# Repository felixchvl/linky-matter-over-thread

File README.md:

# linky-matter-over-thread

A small board that connects to the TIC output of a French Linky meter and makes its readings available over Thread, as a Matter device. It is powered by the meter itself, so there is no battery to replace and no power supply to run to the meter.

## Why I made it

I wanted my electricity usage in Home Assistant, live and without any cloud. The usual options are a Zigbee dongle (ZLinky), a Wi-Fi board that needs a USB supply next to the meter, or the Enedis website a day later. My home already runs a Thread network, and Home Assistant reads Matter energy measurements natively (kWh for the Energy dashboard, plus W, VA and V). So this board speaks Thread and Matter, and nothing else.

The closest thing I found is [BDeliers' Elektor Labs entry](https://www.elektormagazine.com/labs/the-electric-meter-that-matters) from 2024, which runs Matter over Thread on an STM32WB dev kit. The kit draws more than the TIC can supply, so it needs its own power. Running from the meter alone is the whole point of this one.

## Status

- [x] Schematic, v1
- [x] PCB layout, v1 (DRC clean, matches the schematic)
- [ ] First boards ordered and soldered
- [ ] Firmware (Zephyr / nRF Connect SDK, Matter over Thread)
  - [x] TIC decoder for both modes, with host tests
  - [x] Board definition and Matter application, building with nRF Connect SDK v3.4.2
  - [x] Energy per tariff index in Matter (HC/HP, Tempo, up to 10 indexes)
  - [ ] Running on a real board
- [x] Case designed in FreeCAD, checked against the board's 3D model (not printed yet)

Nothing has been built yet, so treat it as a design in progress. Read the checklist under [Building one](#building-one) before ordering.

## How it works

The TIC output has three screw terminals. I1 and A provide a little power (at least 130 mW, 6 V rms at 50 kHz). I1 and I2 carry the data as a 50 kHz carrier: carrier present means bit 0. The format is 7E1, at 1200 baud in "historique" mode or 9600 baud in "standard" mode.

**Power.** Two BAT54S form a Schottky bridge on I1–A. A 20 V zener keeps the input well under the 28 V limit of the regulator. A 470 µF capacitor covers the radio's transmit peaks, and a Microchip MCP1804 LDO (SOT-223) makes 3.3 V. With a linear regulator, current is what matters: the TIC can deliver roughly 16–20 mA, and the board should average 1–2 mA as a sleepy Thread device. JP1 links the regulator to the 3.3 V rail. Pull it to run the board from the programming header, or to put an ammeter in its place.

**Data.** The receiver is the stage from Charles-Henri Hallard's PiTInfo: a 2 kΩ trimmer, an LTV-814 optocoupler and a small N-MOSFET (an AO3400A here, a CJ2302 on the PiTInfo). When the carrier is present, TIC_RX goes low, so the UART reads the bits without any inversion. R1, on the MOSFET gate, is 3.3 kΩ as on the PiTInfo since V1.3a: with the 10 kΩ of V1.2 the optocoupler switches off too slowly for 9600 baud. The nRF52840 UART has no 7-bit mode, so the firmware reads 8 bits, checks the parity bit itself and drops it. On top of that, the checksum at the end of each TIC line catches errors. The firmware also keeps the 32 MHz crystal running while it reads the TIC, because the internal RC clock is too loose for 9600 baud.

**Radio.** The radio is an Ebyte E73-2G4M08S1C module with an nRF52840:
- normal voltage mode (VDDH tied to VDD), USB unused;
- a 32.768 kHz crystal (9 pF load, 3.2 × 1.5 mm) with 10 pF capacitors, for accurate wake-ups while sleeping. Nordic's reference uses 12 pF, which Reichelt does not stock in 0805; the lighter load runs the crystal 10 to 35 ppm fast, and cold slows it down, so the firmware declares a 100 ppm clock instead of 50;
- only the 28 castellated pads on the module's edge are used, so it solders with a regular iron; the 15 pads underneath stay unconnected.

The firmware will also read its own input voltage through a divider on AIN6. It will run as a sleepy end device by default, and only become a Thread router if the measured margin allows it.

## Pin assignment

| Signal | nRF52840 | E73 pad |
| --- | --- | --- |
| TIC_RX (UART RX) | P0.13 | 33 |
| Debug UART TX | P0.24 | 35 |
| VIN_SENSE (VIN × 0.13) | P0.30 / AIN6 | 10 |
| Button (to GND, internal pull-up) | P0.02 | 7 |
| LED (active high) | P1.10 | 2 |
| 32.768 kHz crystal | P0.00, P0.01 | 11, 13 |
| Reset | P0.18 | 26 |
| SWDIO, SWDCLK | | 37, 39 |

J2 is a 2.54 mm header, in the same order as the module pads: 3V3, GND, RST, TX, DIO, CLK.

## Files

```
hardware/
  linky-matter-over-thread.kicad_pro, .kicad_sch, .kicad_pcb  KiCad 10 project
  linky-matter-over-thread.kicad_sym, .pretty/                E73 symbol and footprint
  linky-matter-over-thread.3dshapes/                          simplified 3D model of the module
  production/linky-matter-over-thread-gerbers.zip             Gerbers and drill files
  production/bom.csv                                          parts list with Reichelt article numbers
firmware/                                                   Zephyr / nRF Connect SDK app, see firmware/README.md
case/                                                       3D-printed enclosure (FreeCAD), see case/README.md
docs/
  schematic.pdf
  images/
```

| Top | Bottom |
| --- | --- |
|  |  |

The copper alone, with the ground pour hidden so the tracks are easy to follow. The bottom layer is seen through the board, in the same orientation as the top.

| Top copper | Bottom copper |
| --- | --- |
|  |  |

The full schematic is in [docs/schematic.pdf](docs/schematic.pdf).

## Building one

The board is 64 × 41 mm, two layers, 1.6 mm. The Gerber zip can be uploaded as is to JLCPCB or any other fab. JLCPCB no longer adds an order number by default ("Mark on PCB: Remove Mark"), so the board has no placeholder for one.

Tracks are 0.5 mm for power and ground, 0.4 mm for signals and 0.3 mm on the module's pads, with at least 0.25 mm between copper, well clear of standard process limits. Silkscreen text is at least 1 mm high with a 0.15 mm stroke. The rules are saved in the KiCad project (Default and Power netclasses), so edits in KiCad pick them up. There is no copper on either layer between the module's antenna end and the board edge.

To regenerate the Gerber zip after a change, from `hardware/`:

```
kicad-cli pcb export gerbers --layers F.Cu,B.Cu,F.Paste,B.Paste,F.SilkS,B.SilkS,F.Mask,B.Mask,Edge.Cuts --subtract-soldermask -o gerbers/ linky-matter-over-thread.kicad_pcb
kicad-cli pcb export drill --format excellon --excellon-units mm --excellon-separate-th --generate-map --map-format gerberx2 -o gerbers/ linky-matter-over-thread.kicad_pcb
```

Then zip the contents of `gerbers/` into `production/linky-matter-over-thread-gerbers.zip`.

Before ordering:

- The E73 footprint is drawn from Ebyte's drawing. Its pads match the [SnapEDA footprint](https://github.com/rbaron/b-parasite/tree/main/kicad/lib/snapeda) and [nordic-lib-kicad](https://github.com/hlord2000/nordic-lib-kicad) exactly, and [nrfmicro](https://github.com/joric/nrfmicro)'s within 0.2 mm, but it has not met a physical module yet. If you have one, print [docs/footprint-check-1to1.pdf](docs/footprint-check-1to1.pdf) at 100 % (its two scale bars tell you if the printer resized it) and lay the module on it.
- The E73 is no longer listed at LCSC, and Passion Radio has run out. [Micros](https://www.micros.com.pl/en/product/rf-e73-2g4m08s1c,355348.html) (Poland) and [Ebyte's own store](https://ebyteiot.com/products/2-4ghz-ble-mesh-small-smd-e73-2g4m08s1c-nordic-nrf52840-module-small-size-ble-5-0) sell it. Make sure it is the E73-2G4M08S1C: the S1E carries an nRF52833, and the S1CX is a different variant.
- Every other part is stocked by Reichelt, an EU distributor. I picked it on purpose: since 2026, small parcels from China into France pay a flat customs fee per type of item, which costs more than the parts on an order like this one.

Parts:

- **[production/bom.csv](hardware/production/bom.csv)** has every part with a manufacturer part number and its Reichelt article number.
- **Passives:** generic 0805, any equivalent works. Add a 4.7 kΩ in case R1 needs tuning on your meter (see below).
- **Regulator:** the MCP1804 takes up to 28 V in (30 V absolute), which leaves a wide margin over the 20 V zener.

Soldering:

- All SMD parts are 0805, SOT-23, SOT-223, MiniMELF or a 3.2 × 1.5 mm crystal, with hand-soldering pads where KiCad has them.
- The 3.2 × 1.5 mm crystal and the 0805 parts are the smallest; a fine tip is enough, hot air helps.

Before connecting it to the meter:

- Set RV1 to about 1–1.2 kΩ. The TIC wants 500–2000 Ω on its data pair, and 1–1.2 kΩ is what people report working on Linky.
- Wire A, I1 and I2 as printed next to the terminal. I1 is in the middle because it feeds both the power bridge and the receiver, so the order differs from the meter's.
- Only use the meter's I1, I2 and A terminals. The dry contact (C1, C2) next to them can carry 230 V, and the board has no protection against it. With a standard off-peak contactor, its coil limits the current to about 13 mA. The board survives that, but it keeps the contactor on, so the water heater keeps heating. With any other wiring, RV1 can burn. A fuse would not help: in the standard case the fault current is about the same as the board's normal current.
- So before screwing the wires into the board, measure the AC voltage between each pair of wires (A–I1, I1–I2, A–I2) with a multimeter, during peak hours, while the dry contact is open (during off-peak hours C1–C2 reads 0 V). Nothing should read more than about 15 V. The TIC itself shows a few volts at most, often less because multimeters under-read its 50 kHz carrier. A reading near 230 V means a wire is on the wrong terminal.
- Never feed 3.3 V into J2 while JP1 is fitted.
- When a computer is plugged into J2 at the meter, run it on battery or through a USB isolator. The board's ground is tied to I1 and A through the bridge, so an earthed computer would tie the TIC to earth.

First power-up on the meter, if you have a multimeter and a scope:

- 3.3 V on the 3V3 test point, and VIN well above 4 V (the regulator needs 3.7 V).
- The 3.3 V rail should rise from 0 to 1.7 V in less than 60 ms, or the nRF52840's power-on reset may misbehave. If it is slower, a smaller C1 (220 µF) still covers the radio's peaks.
- TIC_RX on the RX test point, at 1200 baud (historique) and 9600 baud (standard): square edges, low while the carrier is on. If frames are missing, lower RV1 a little, but not under about 600 Ω so the TIC still sees more than 500 Ω. If the meter stays in historique mode and its signal is weak, R1 can go back up to 4.7 kΩ for more sensitivity.
- The average current, with an ammeter in place of JP1.

The module is programmed over SWD through J2, with a J-Link or a Raspberry Pi Pico running [debugprobe](https://github.com/raspberrypi/debugprobe).

## Credits

- The TIC receiver comes from [PiTInfo](https://github.com/hallard/teleinfo) by Charles-Henri Hallard.
- The electrical and frame details come from the Enedis TIC specification, Enedis-NOI-CPT_54E.
- The module pinout and pad drawing come from the Ebyte E73-2G4M08S1C user manual.
- Decoding in the firmware will start from [zephyr-linky-tic](https://github.com/lucasdietrich/zephyr-linky-tic) by Lucas Dietrich.

## License

The hardware design (everything outside `firmware/`) is shared under [CC BY-NC-SA 4.0](LICENSE), the same license as the PiTInfo design it builds on.

The firmware is under the [Apache License 2.0](firmware/LICENSE), like Zephyr.

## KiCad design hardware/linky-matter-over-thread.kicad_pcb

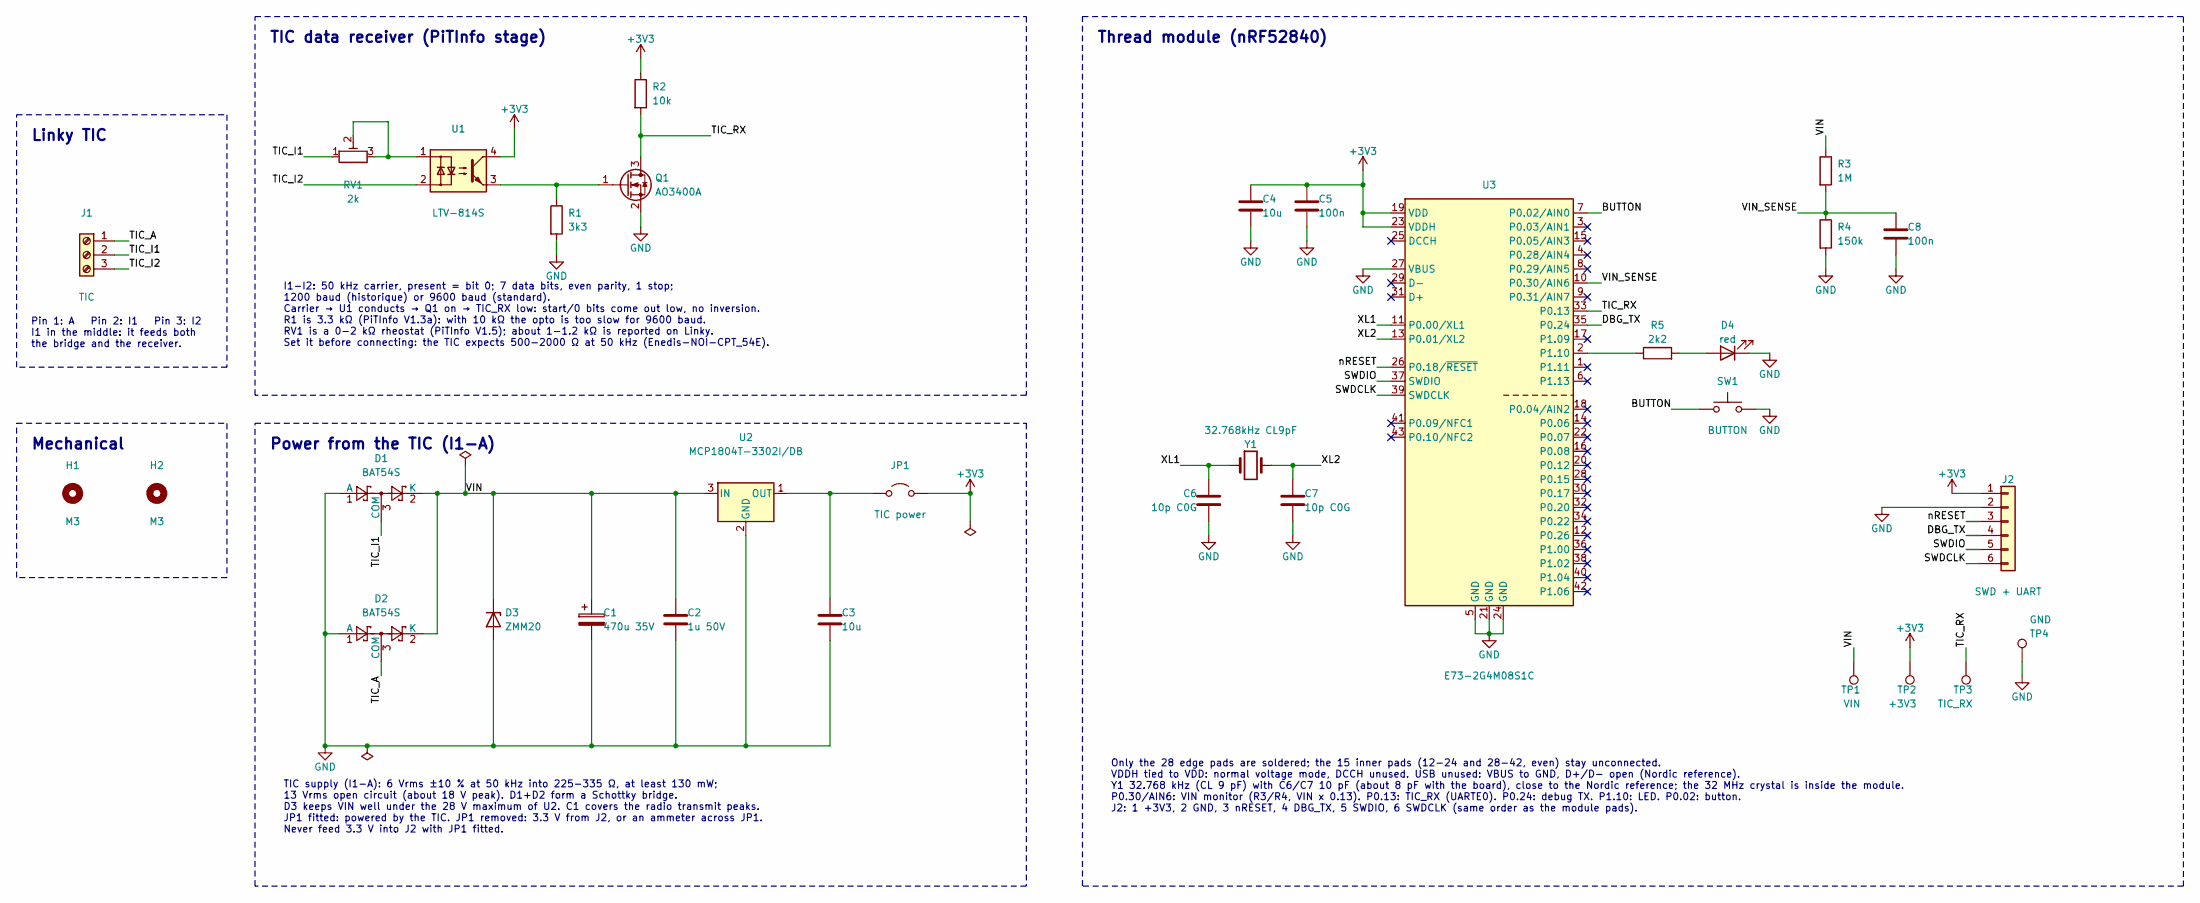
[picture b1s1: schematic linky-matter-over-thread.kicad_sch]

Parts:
C1: 470u 35V; CP_Radial_D10.0mm_P5.00mm; MPN RD1V477M10016BB100
C2: 1u 50V; C_0805_2012Metric_Pad1.18x1.45mm_HandSolder; MPN CL21B105KBFNNNE
C3, C4: 10u; C_0805_2012Metric_Pad1.18x1.45mm_HandSolder; MPN CL21B106KOQNNNE
C5, C8: 100n; C_0805_2012Metric_Pad1.18x1.45mm_HandSolder; MPN CL21B104KBCNNNC
C6, C7: 10p C0G; C_0805_2012Metric_Pad1.18x1.45mm_HandSolder; MPN CC0805JRNPO9BN100
D1, D2: BAT54S; SOT-23; MPN BAT54S-7-F
D3: ZMM20; D_MiniMELF; MPN ZMM20V (MiniMELF, 0.5 W)
D4: red; LED_0805_2012Metric_Pad1.15x1.40mm_HandSolder; MPN 17-21/R6C-AP1Q2L/3T
H1, H2: M3; MountingHole_3.2mm_M3
J1: TIC; TerminalBlock_Phoenix_MKDS-1,5-3-5.08_1x03_P5.08mm_Horizont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; MPN MKDS 1,5/ 3-5,08
J2: SWD + UART; PinHeader_1x06_P2.54mm_Vertical; MPN 6 pins cut from a 1x40 2.54 mm header
JP1: TIC power; PinHeader_1x02_P2.54mm_Vertical; MPN 2 pins cut from the same header, plus a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
Q1: AO3400A; SOT-23; MPN AO3400A
R1: 3k3; R_0805_2012Metric_Pad1.20x1.40mm_HandSolder; MPN 3.3 k 0805
R2: 10k; R_0805_2012Metric_Pad1.20x1.40mm_HandSolder; MPN 10 k 0805
R3: 1M; R_0805_2012Metric_Pad1.20x1.40mm_HandSolder; MPN 1 M 0805
R4: 150k; R_0805_2012Metric_Pad1.20x1.40mm_HandSolder; MPN 150 k 0805
R5: 2k2; R_0805_2012Metric_Pad1.20x1.40mm_HandSolder; MPN 2.2 k 0805
RV1: 2k; Potentiometer_Bourns_3296W_Vertical; MPN 64W 2 k multi-turn trimmer (3296W footp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
SW1: BUTTON; SW_PUSH_6mm; MPN DTS-62N (6 x 6 x 5 mm)
TP1: VIN; TestPoint_Pad_D1.5mm
TP2: +3V3; TestPoint_Pad_D1.5mm
TP3: TIC_RX; TestPoint_Pad_D1.5mm
TP4: GND; TestPoint_Pad_D1.5mm
U1: LTV-814S; SMDIP-4_W9.53mm; MPN LTV-814S
U2: MCP1804T-3302I/DB; SOT-223-3_TabPin2; MPN MCP1804T-3302I/DB
U3: E73-2G4M08S1C; MPN E73-2G4M08S1C
Y1: 32.768kHz CL9pF; Crystal_SMD_3215-2Pin_3.2x1.5mm; MPN CC7V-T1A 32.768 kHz 9 pF

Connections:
+3V3: C4.1, C5.1, J2.1, JP1.2 (B), R2.1, TP2.1, U1.4, U3.19 (VDD), U3.23 (VDDH)
/BUTTON: SW1.1, U3.7 (P0.02/AIN0)
/DBG_TX: J2.4, U3.35 (P0.24)
/SWDCLK: J2.6, U3.39 (SWDCLK)
/SWDIO: J2.5, U3.37 (SWDIO)
/TIC_A: D2.3 (COM), J1.1
/TIC_I1: D1.3 (COM), J1.2, RV1.1
/TIC_I2: J1.3, U1.2
/TIC_RX: Q1.3 (D), R2.2, TP3.1, U3.33 (P0.13)
/VIN: C1.1, C2.1, D1.2 (K), D2.2 (K), D3.1 (K), R3.1, TP1.1, U2.3 (IN)
/VIN_SENSE: C8.1, R3.2, R4.1, U3.10 (P0.30/AIN6)
/XL1: C6.1, U3.11 (P0.00/XL1), Y1.1
/XL2: C7.1, U3.13 (P0.01/XL2), Y1.2
/nRESET: J2.3, U3.26 (P0.18/~RESET)
GND: C1.2, C2.2, C3.2, C4.2, C5.2, C6.2, C7.2, C8.2, D1.1 (A), D2.1 (A), D3.2 (A), D4.1 (K), J2.2, Q1.2 (S), R1.2, R4.2, SW1.2, TP4.1, U2.2 (GND), U3.5 (GND), U3.21 (GND), U3.24 (GND), U3.27 (VBUS)
unnamed: D4.2 (A), R5.2
unnamed: C3.1, JP1.1 (A), U2.1 (OUT)
unnamed: Q1.1 (G), R1.1, U1.3
unnamed: RV1.2, RV1.3, U1.1
unnamed: R5.1, U3.2 (P1.10)

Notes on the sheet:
Power from the TIC (I1-A)
TIC data receiver (PiTInfo stage)
I1-I2: 50 kHz carrier, present = bit 0; 7 data bits, even parity, 1 stop; 1200 baud (historique) or 9600 baud (standard). Carrier → U1 conducts → Q1 on → TIC_RX low: start/0 bits come out low, no inversion. R1 is 3.3 kΩ (PiTInfo V1.3a): with 10 kΩ the opto is too slow for 9600 baud. RV1 is a 0-2 kΩ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
Thread module (nRF52840)
Only the 28 edge pads are soldered; the 15 inner pads (12-24 and 28-42, even) stay unconnected. VDDH tied to VDD: normal voltage mode, DCCH unused. USB unused: VBUS to GND, D+/D- open (Nordic reference). Y1 32.768 kHz (CL 9 pF) with C6/C7 10 pF (about 8 pF with the board), close to the Nordic refer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
TIC supply (I1-A): 6 Vrms ±10 % at 50 kHz into 225-335 Ω, at least 130 mW; 13 Vrms open circuit (about 18 V peak). D1+D2 form a Schottky bridge. D3 keeps VIN well under the 28 V maximum of U2. C1 covers the radio transmit peaks. JP1 fitted: powered by the TIC. JP1 removed: 3.3 V from J2, or an amme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
Linky TIC
Pin 1: A Pin 2: I1 Pin 3: I2 I1 in the middle: it feeds both the bridge and the receiver.
Mechanical

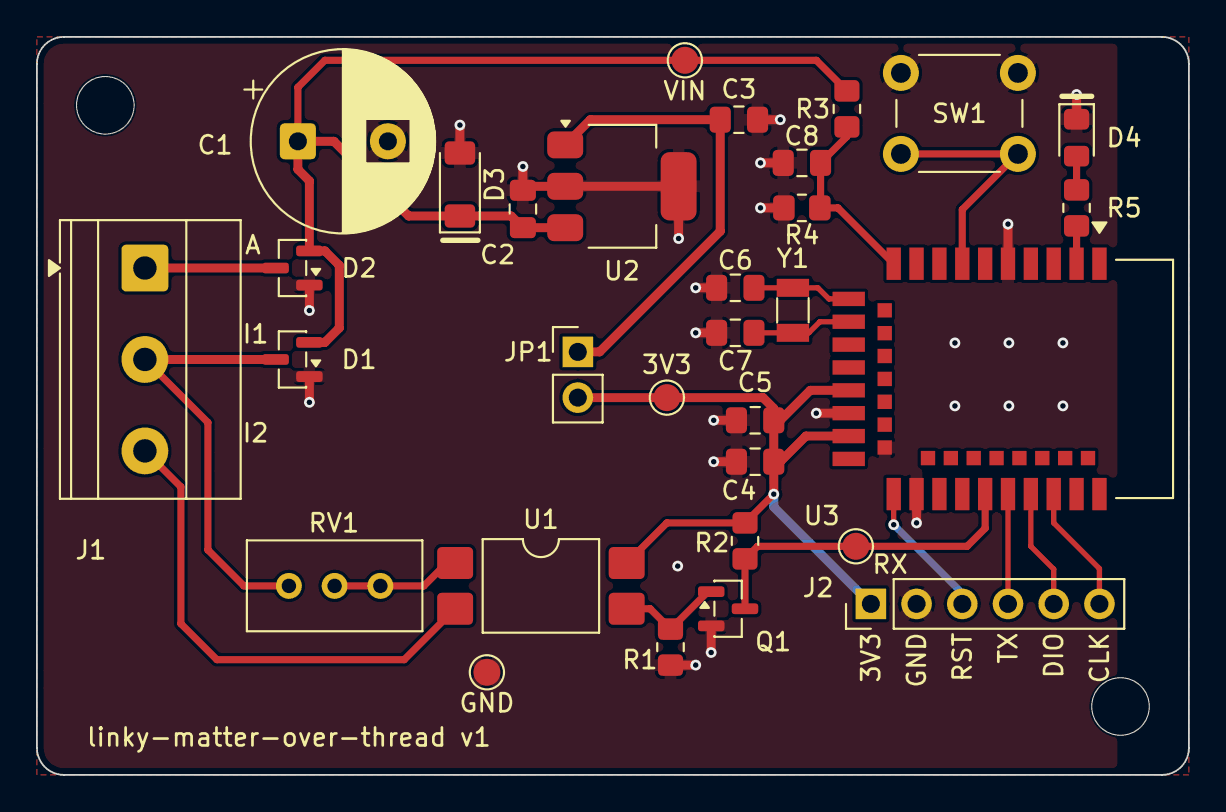
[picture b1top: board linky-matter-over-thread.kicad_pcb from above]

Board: 2 copper layers, 64.0 x 41.0 mm, 33 parts (0 on the bottom side), 20 nets.

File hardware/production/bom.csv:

"References","Qty","Value","Footprint","Manufacturer","MPN","Reichelt"
"C1","1","470u 35V","Capacitor_THT:CP_Radial_D10.0mm_P5.00mm","Samwha","RD1V477M10016BB100","RD1V477M10016100"
"C2","1","1u 50V","Capacitor_SMD:C_0805_2012Metric_Pad1.18x1.45mm_HandSolder","Samsung","CL21B105KBFNNNE","CL21B105KBFNNNE"
"C3,C4","2","10u","Capacitor_SMD:C_0805_2012Metric_Pad1.18x1.45mm_HandSolder","Samsung","CL21B106KOQNNNE","CL21B106KOQNNNE"
"C5,C8","2","100n","Capacitor_SMD:C_0805_2012Metric_Pad1.18x1.45mm_HandSolder","Samsung","CL21B104KBCNNNC","CL21B104KBCNNNC"
"C6,C7","2","10p C0G","Capacitor_SMD:C_0805_2012Metric_Pad1.18x1.45mm_HandSolder","Yageo","CC0805JRNPO9BN100","NPO-G0805 10P"
"D1,D2","2","BAT54S","Package_TO_SOT_SMD:SOT-23","Diodes Inc.","BAT54S-7-F","BAT54S-7-F"
"D3","1","ZMM20","Diode_SMD:D_MiniMELF","Hottech","ZMM20V (MiniMELF, 0.5 W)","SMD ZF 20"
"D4","1","red","LED_SMD:LED_0805_2012Metric_Pad1.15x1.40mm_HandSolder","Everlight","17-21/R6C-AP1Q2L/3T","EVL 17-21/R6C-A"
"J1","1","TIC","TerminalBlock_Phoenix:TerminalBlock_Phoenix_MKDS-1,5-3-5.08_1x03_P5.08mm_Horizontal","Phoenix Contact","MKDS 1,5/ 3-5,08","MKDS 1,5 3 5,08"
"J2","1","SWD + UART","Connector_PinHeader_2.54mm:PinHeader_1x06_P2.54mm_Vertical","Econ Connect","6 pins cut from a 1x40 2.54 mm header","ECON SL40G1"
"JP1","1","TIC power","Connector_PinHeader_2.54mm:PinHeader_1x02_P2.54mm_Vertical","Econ Connect","2 pins cut from the same header, plus a jumper","ECON SL40G1 + JUMPER 2,54 SW"
"Q1","1","AO3400A","Package_TO_SOT_SMD:SOT-23","Alpha & Omega","AO3400A","AO3400A"
"R1","1","3k3","Resistor_SMD:R_0805_2012Metric_Pad1.20x1.40mm_HandSolder","Yageo","3.3 k 0805","SMD-0805 3,30K"
"R2","1","10k","Resistor_SMD:R_0805_2012Metric_Pad1.20x1.40mm_HandSolder","Yageo","10 k 0805","SMD-0805 10,0K"
"R3","1","1M","Resistor_SMD:R_0805_2012Metric_Pad1.20x1.40mm_HandSolder","Yageo","1 M 0805","SMD-0805 1,00M"
"R4","1","150k","Resistor_SMD:R_0805_2012Metric_Pad1.20x1.40mm_HandSolder","Yageo","150 k 0805","SMD-0805 150K"
"R5","1","2k2","Resistor_SMD:R_0805_2012Metric_Pad1.20x1.40mm_HandSolder","Yageo","2.2 k 0805","SMD-0805 2,20K"
"RV1","1","2k","Potentiometer_THT:Potentiometer_Bourns_3296W_Vertical","no brand (Bourns 3296W clone)","64W 2 k multi-turn trimmer (3296W footprint)","64W-2,0K"
"SW1","1","BUTTON","Button_Switch_THT:SW_PUSH_6mm","Diptronics","DTS-62N (6 x 6 x 5 mm)","DIP DTS-62N"
"U1","1","LTV-814S","Package_DIP:SMDIP-4_W9.53mm","Lite-On","LTV-814S","LTV 814S"
"U2","1","MCP1804T-3302I/DB","Package_TO_SOT_SMD:SOT-223-3_TabPin2","Microchip","MCP1804T-3302I/DB","MCP1804T3302IDB"
"U3","1","E73-2G4M08S1C","linky-matter-over-thread:E73-2G4M08S1C","Ebyte","E73-2G4M08S1C","(not at Reichelt: Micros or the Ebyte store)"
"Y1","1","32.768kHz CL9pF","Crystal:Crystal_SMD_3215-2Pin_3.2x1.5mm","Micro Crystal","CC7V-T1A 32.768 kHz 9 pF","32,768 CC7V-9"
